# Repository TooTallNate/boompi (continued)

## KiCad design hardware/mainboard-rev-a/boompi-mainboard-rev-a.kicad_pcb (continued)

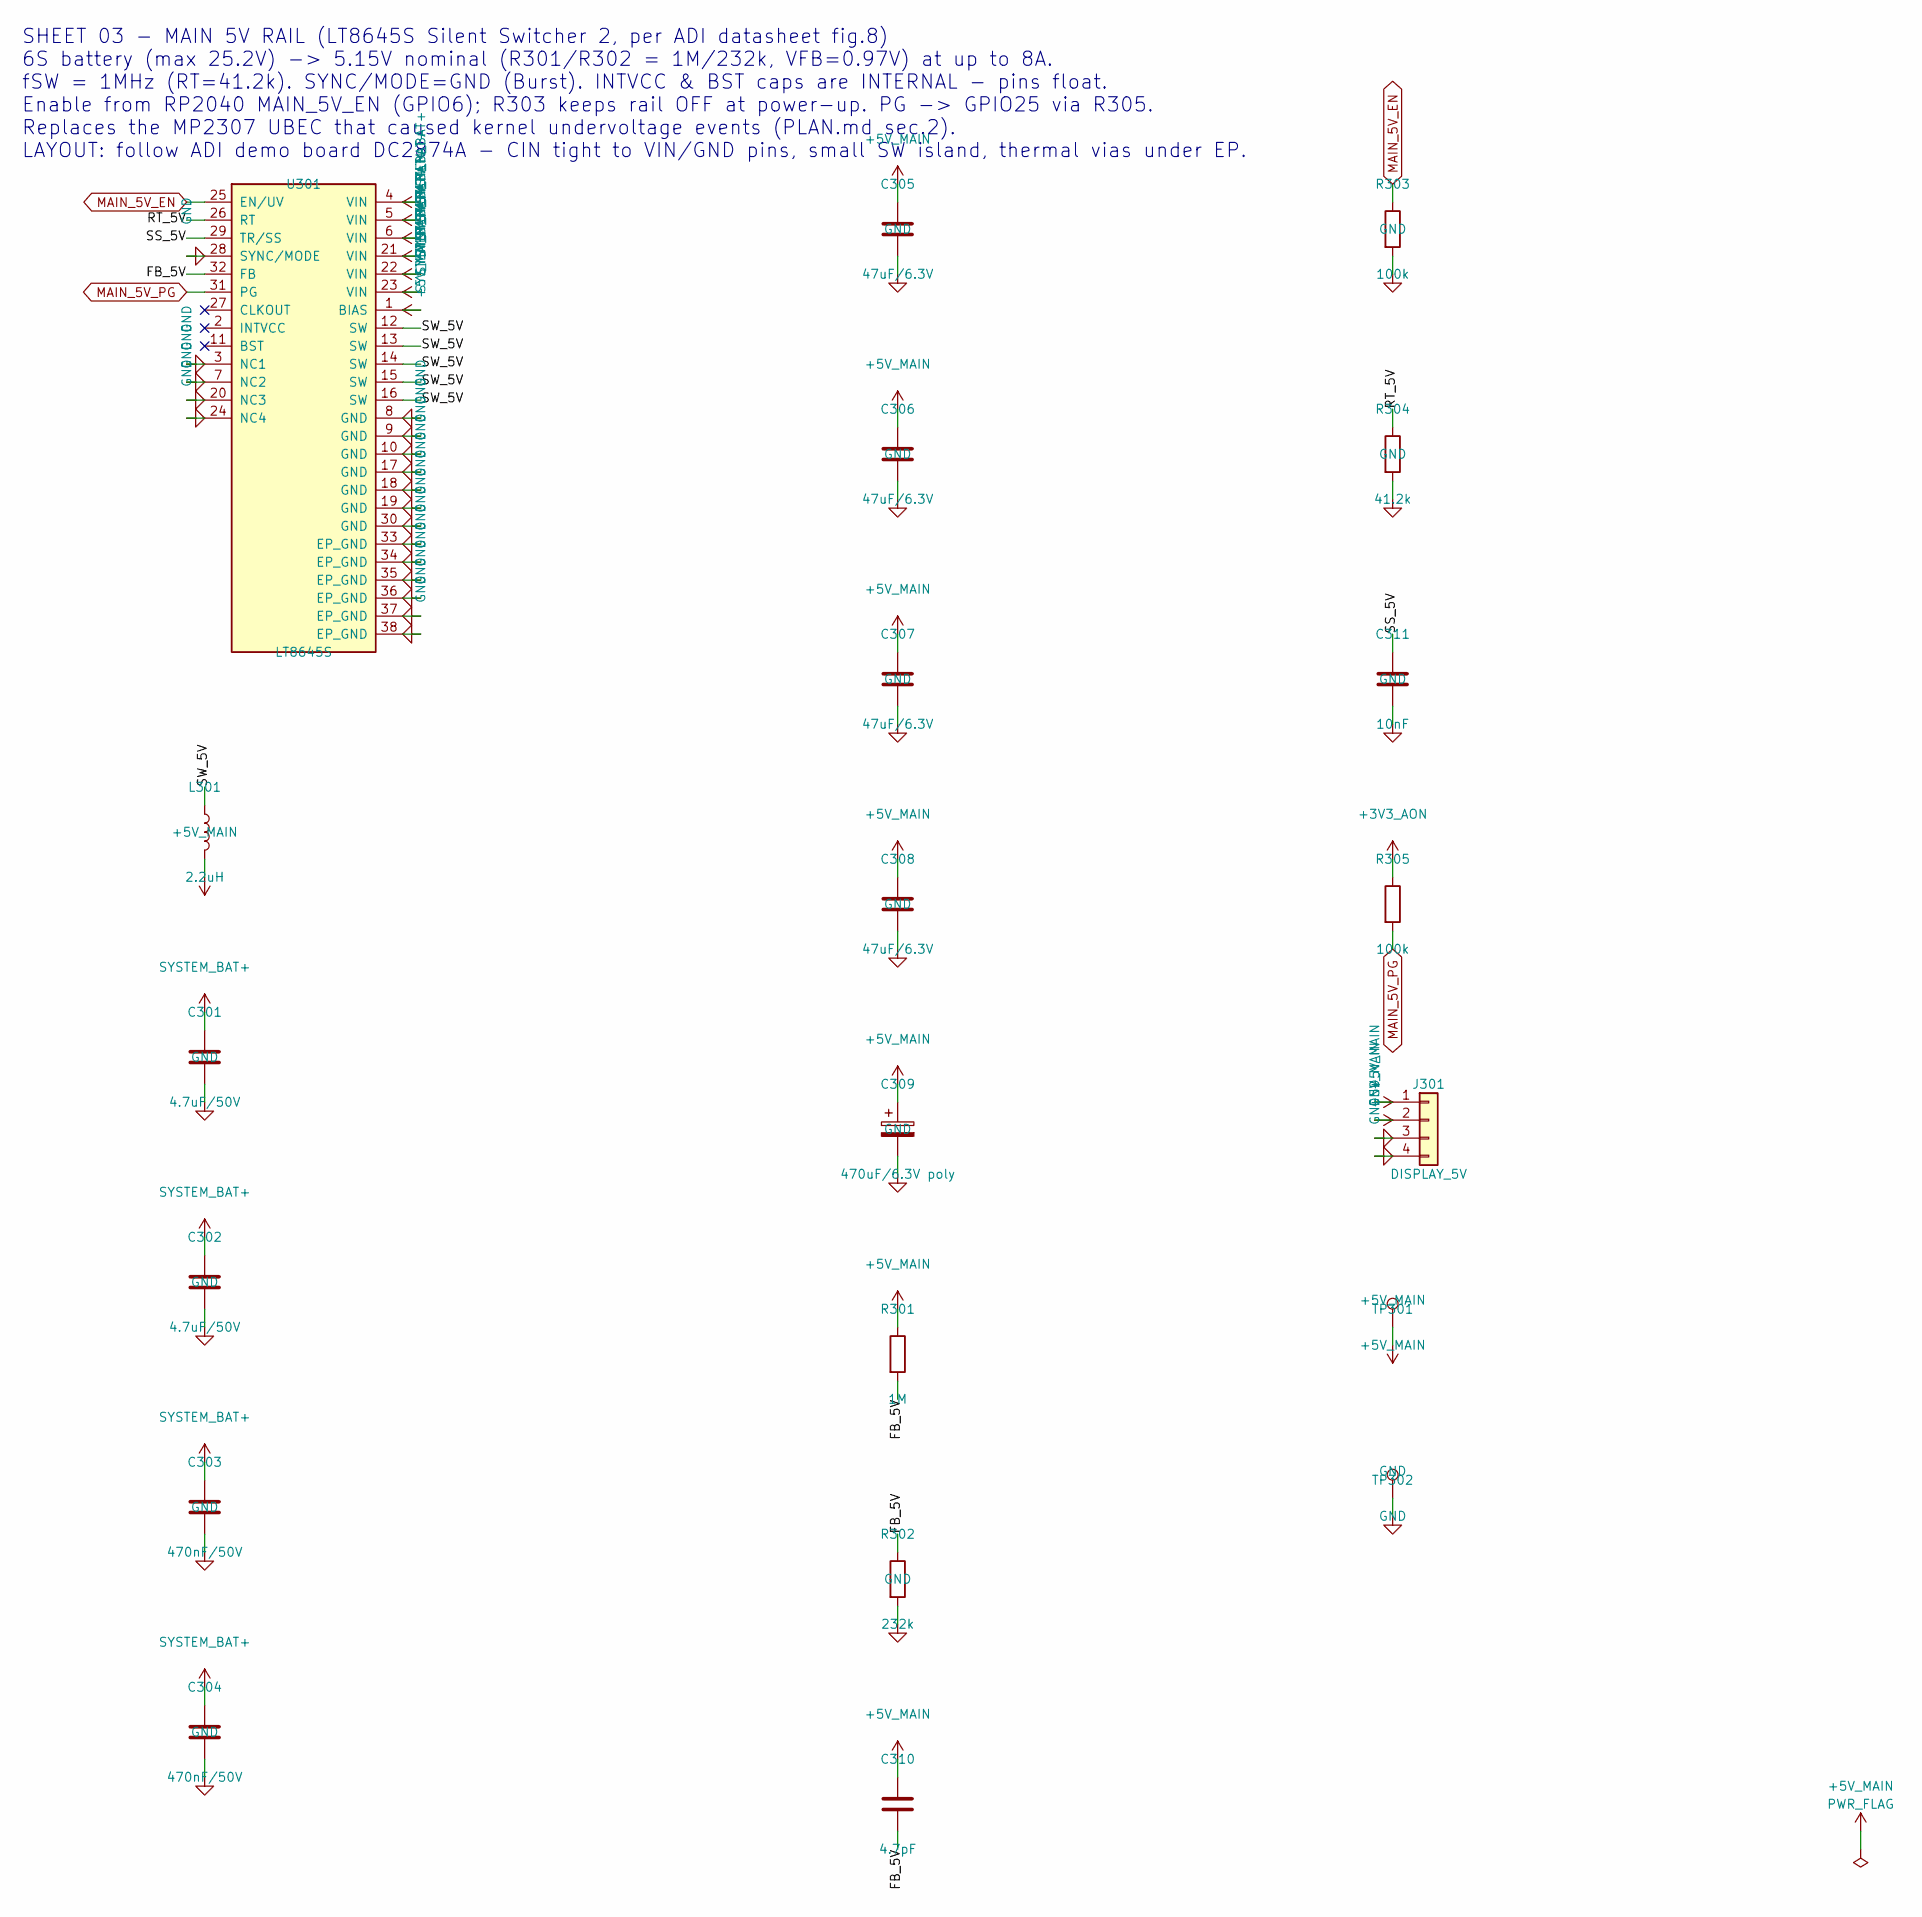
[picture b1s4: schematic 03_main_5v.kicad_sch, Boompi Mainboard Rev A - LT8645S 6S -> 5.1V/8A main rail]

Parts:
C301, C302: 4.7uF/50V; C_1210_3225Metric
C303, C304: 470nF/50V; C_0603_1608Metric
C305, C306, C307, C308: 47uF/6.3V; C_1210_3225Metric
C309: 470uF/6.3V poly; CP_Elec_8x10.5; MPN Panasonic 6TPE470MI
C310: 4.7pF; C_0603_1608Metric
C311: 10nF; C_0603_1608Metric
J301: DISPLAY_5V; JST_XH_B4B-XH-A_1x04_P2.50mm_Vertical; MPN JST B4B-XH-A
L301: 2.2uH; L_Coilcraft_XAL6060-XXX; MPN Coilcraft XEL6060-222MEB
R301: 1M; R_0603_1608Metric
R302: 232k; R_0603_1608Metric
R303, R305: 100k; R_0603_1608Metric
R304: 41.2k; R_0603_1608Metric
TP301: +5V_MAIN; TestPoint_Pad_D1.5mm
TP302: GND; TestPoint_Pad_D1.5mm
U301: LT8645S; LT8645S_LQFN32_4x6mm; MPN ADI LT8645SEV#PBF

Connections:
+3V3_AON: R305.1; also elsewhere on the board
+5V_MAIN: C305.1, C306.1, C307.1, C308.1, C309.1, C310.1, J301.1, J301.2, L301.2, R301.1, TP301.1, U301.1 (BIAS); also elsewhere on the board
/03_MAIN_5V/FB_5V: C310.2, R301.2, R302.1, U301.32 (FB)
/03_MAIN_5V/RT_5V: R304.1, U301.26 (RT)
/03_MAIN_5V/SS_5V: C311.1, U301.29 (TR/SS)
/03_MAIN_5V/SW_5V: L301.1, U301.12 (SW), U301.13 (SW), U301.14 (SW), U301.15 (SW), U301.16 (SW)
GND: C301.2, C302.2, C303.2, C304.2, C305.2, C306.2, C307.2, C308.2, C309.2, C311.2, J301.3, J301.4, R302.2, R303.2, R304.2, TP302.1, U301.3 (NC1), U301.7 (NC2), U301.8 (GND), U301.9 (GND), U301.10 (GND), U301.17 (GND), U301.18 (GND), U301.19 (GND), U301.20 (NC3), U301.24 (NC4), U301.28 (SYNC/MODE), U301.30 (GND), U301.33 (EP_GND), U301.34 (EP_GND), U301.35 (EP_GND), U301.36 (EP_GND), U301.37 (EP_GND), U301.38 (EP_GND); also elsewhere on the board
MAIN_5V_EN: R303.1, U301.25 (EN/UV); also elsewhere on the board
MAIN_5V_PG: R305.2, U301.31 (PG); also elsewhere on the board
SYSTEM_BAT+: C301.1, C302.1, C303.1, C304.1, U301.4 (VIN), U301.5 (VIN), U301.6 (VIN), U301.21 (VIN), U301.22 (VIN), U301.23 (VIN); also elsewhere on the board

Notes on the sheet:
SHEET 03 - MAIN 5V RAIL (LT8645S Silent Switcher 2, per ADI datasheet fig.8) 6S battery (max 25.2V) -> 5.15V nominal (R301/R302 = 1M/232k, VFB=0.97V) at up to 8A. fSW = 1MHz (RT=41.2k). SYNC/MODE=GND (Burst). INTVCC & BST caps are INTERNAL - pins float. Enable from RP2040 MAIN_5V_EN (GPIO6); R303 k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

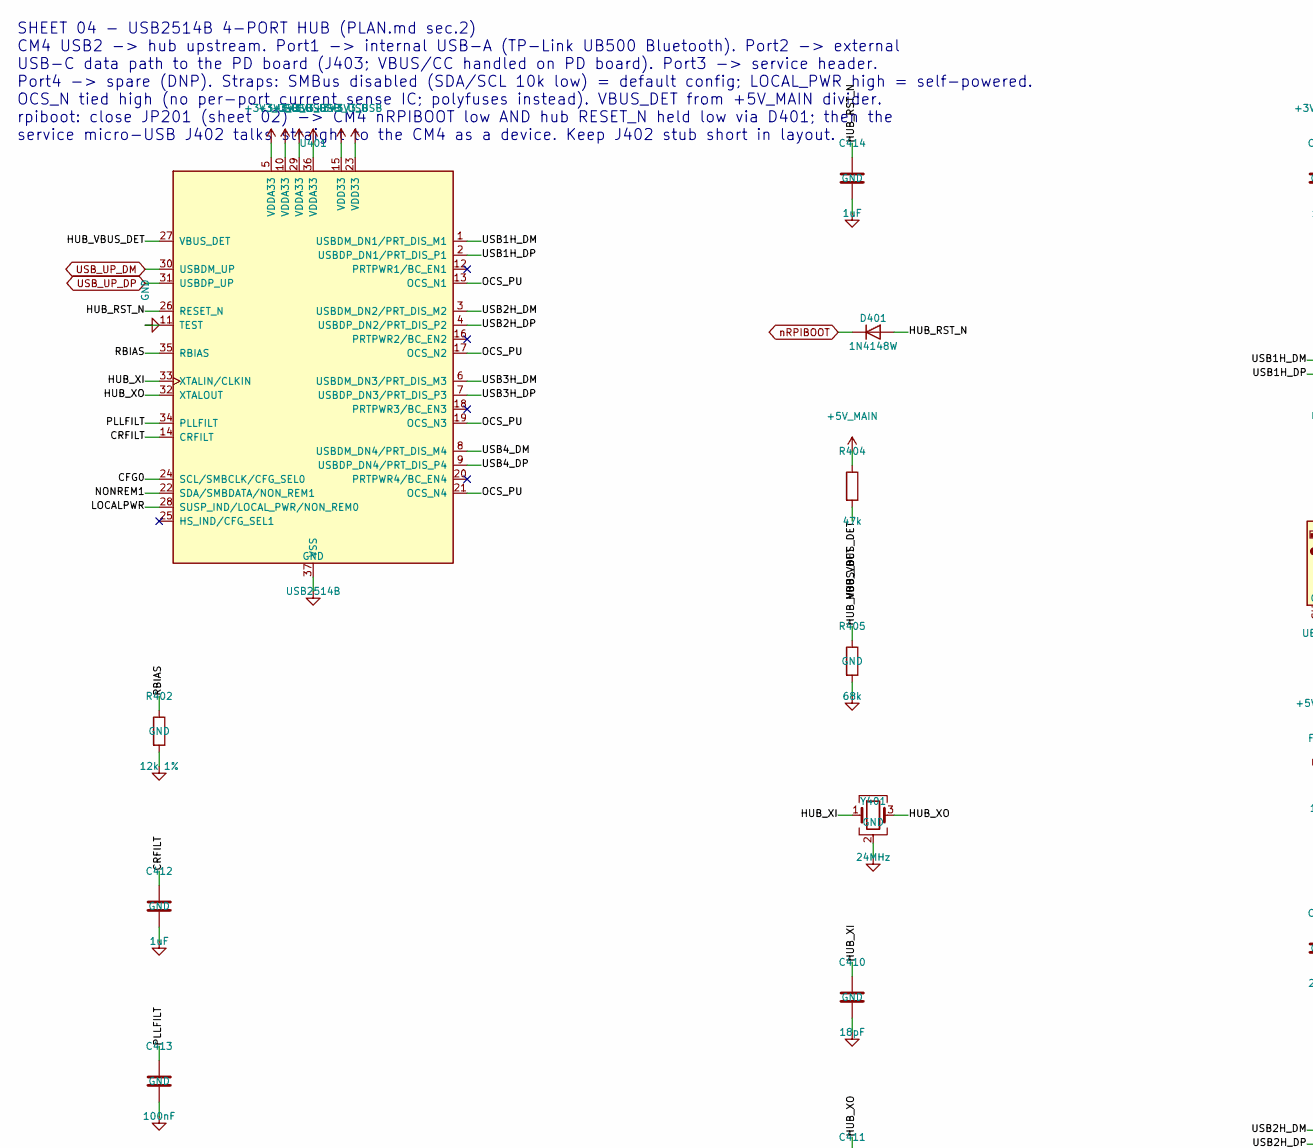
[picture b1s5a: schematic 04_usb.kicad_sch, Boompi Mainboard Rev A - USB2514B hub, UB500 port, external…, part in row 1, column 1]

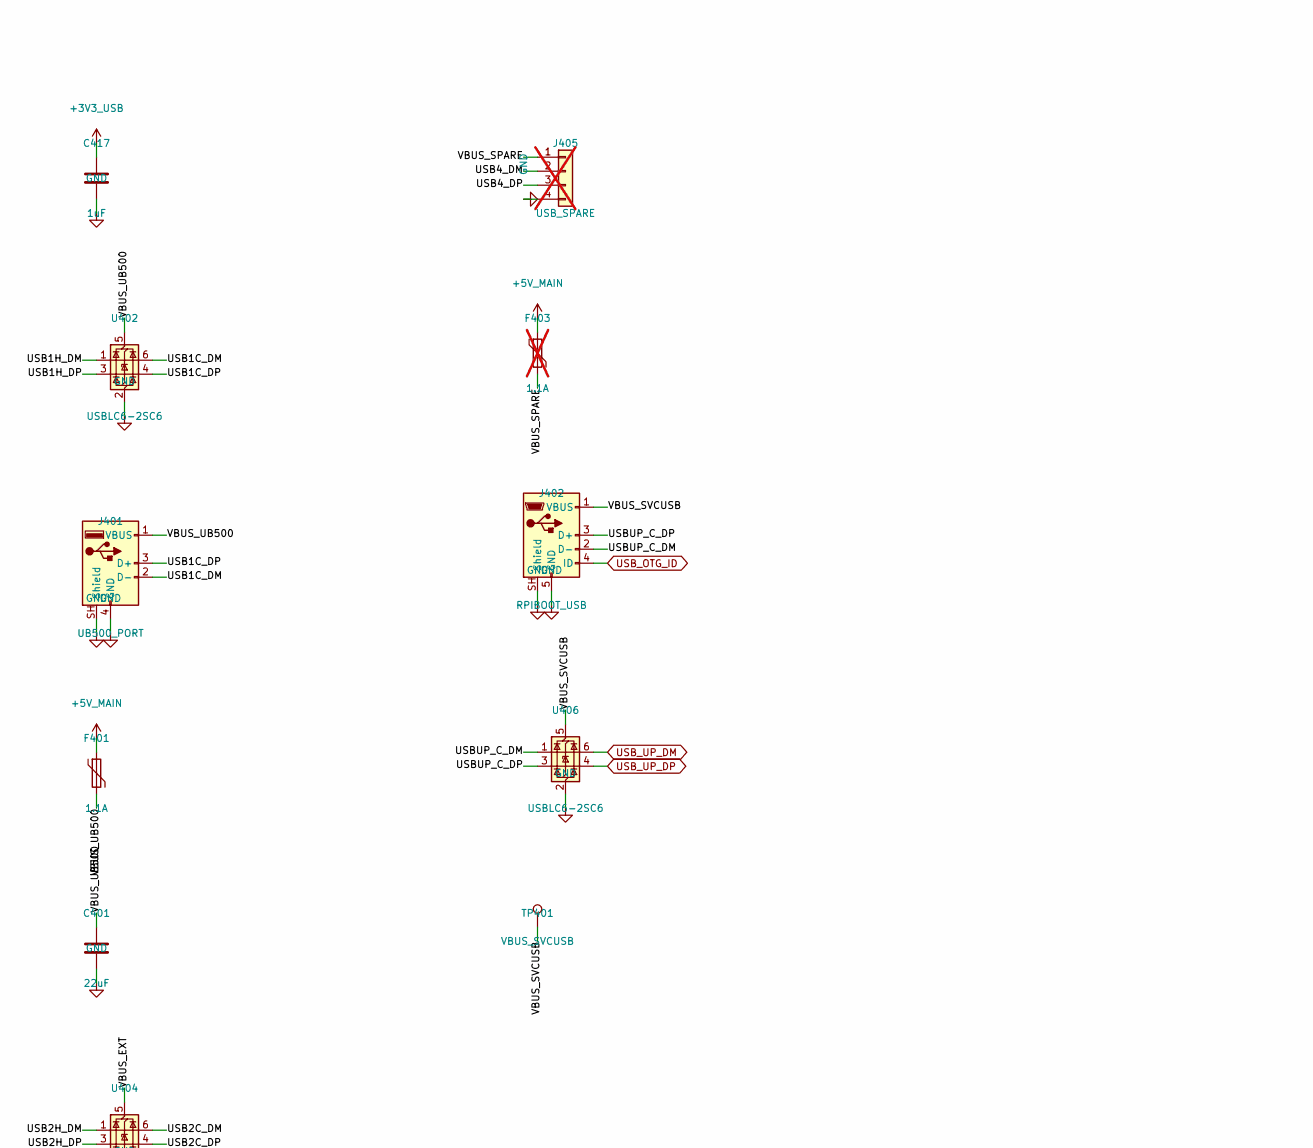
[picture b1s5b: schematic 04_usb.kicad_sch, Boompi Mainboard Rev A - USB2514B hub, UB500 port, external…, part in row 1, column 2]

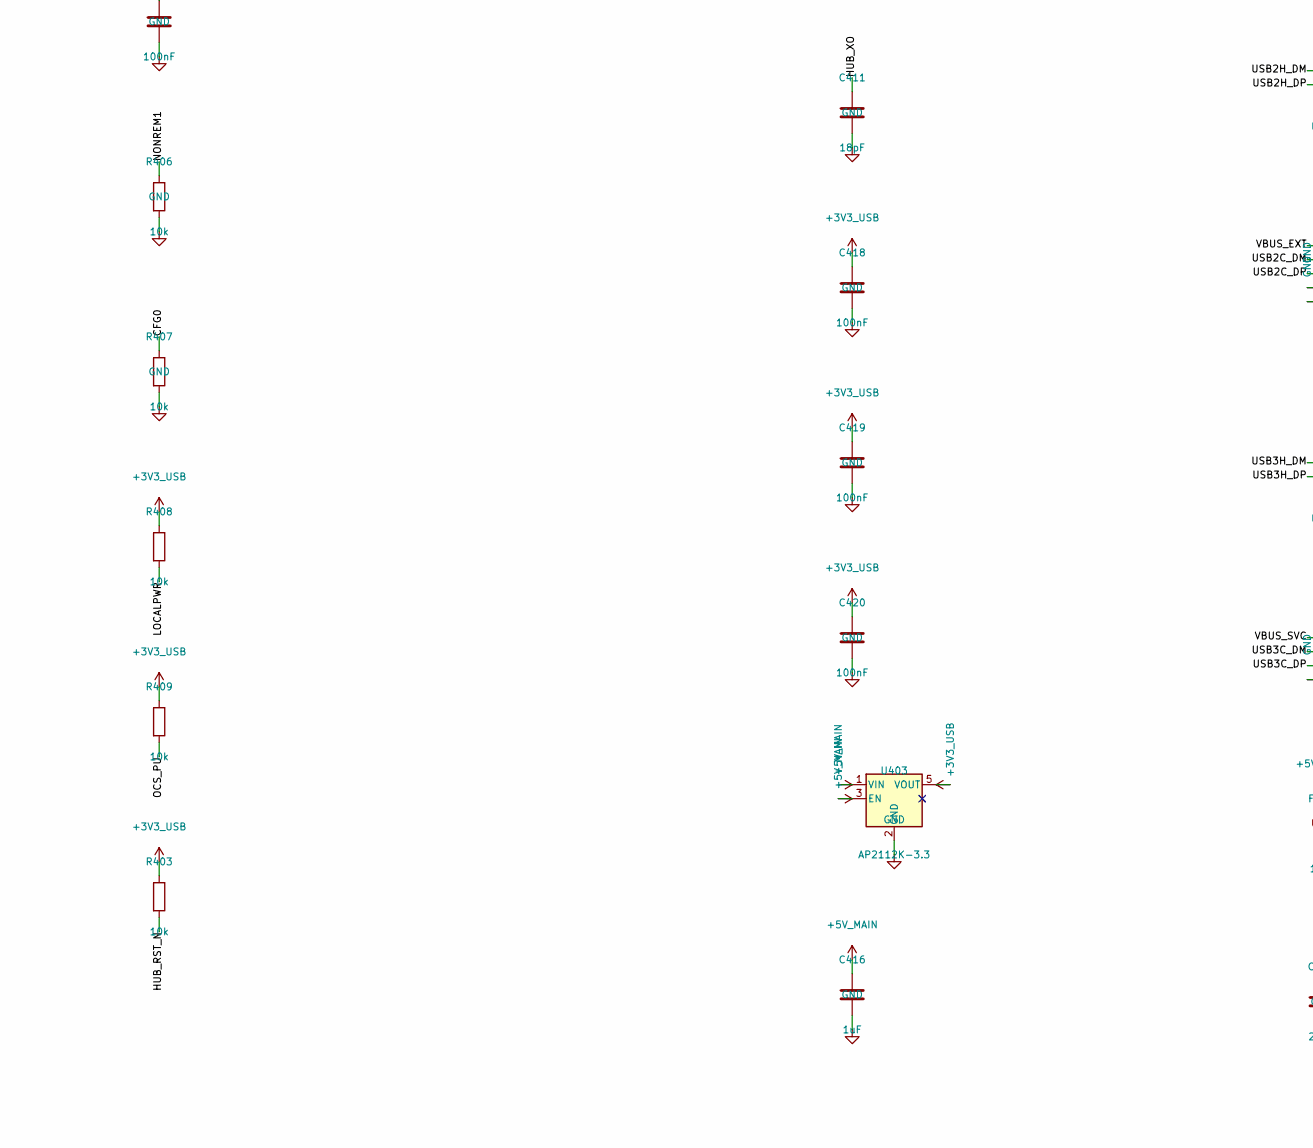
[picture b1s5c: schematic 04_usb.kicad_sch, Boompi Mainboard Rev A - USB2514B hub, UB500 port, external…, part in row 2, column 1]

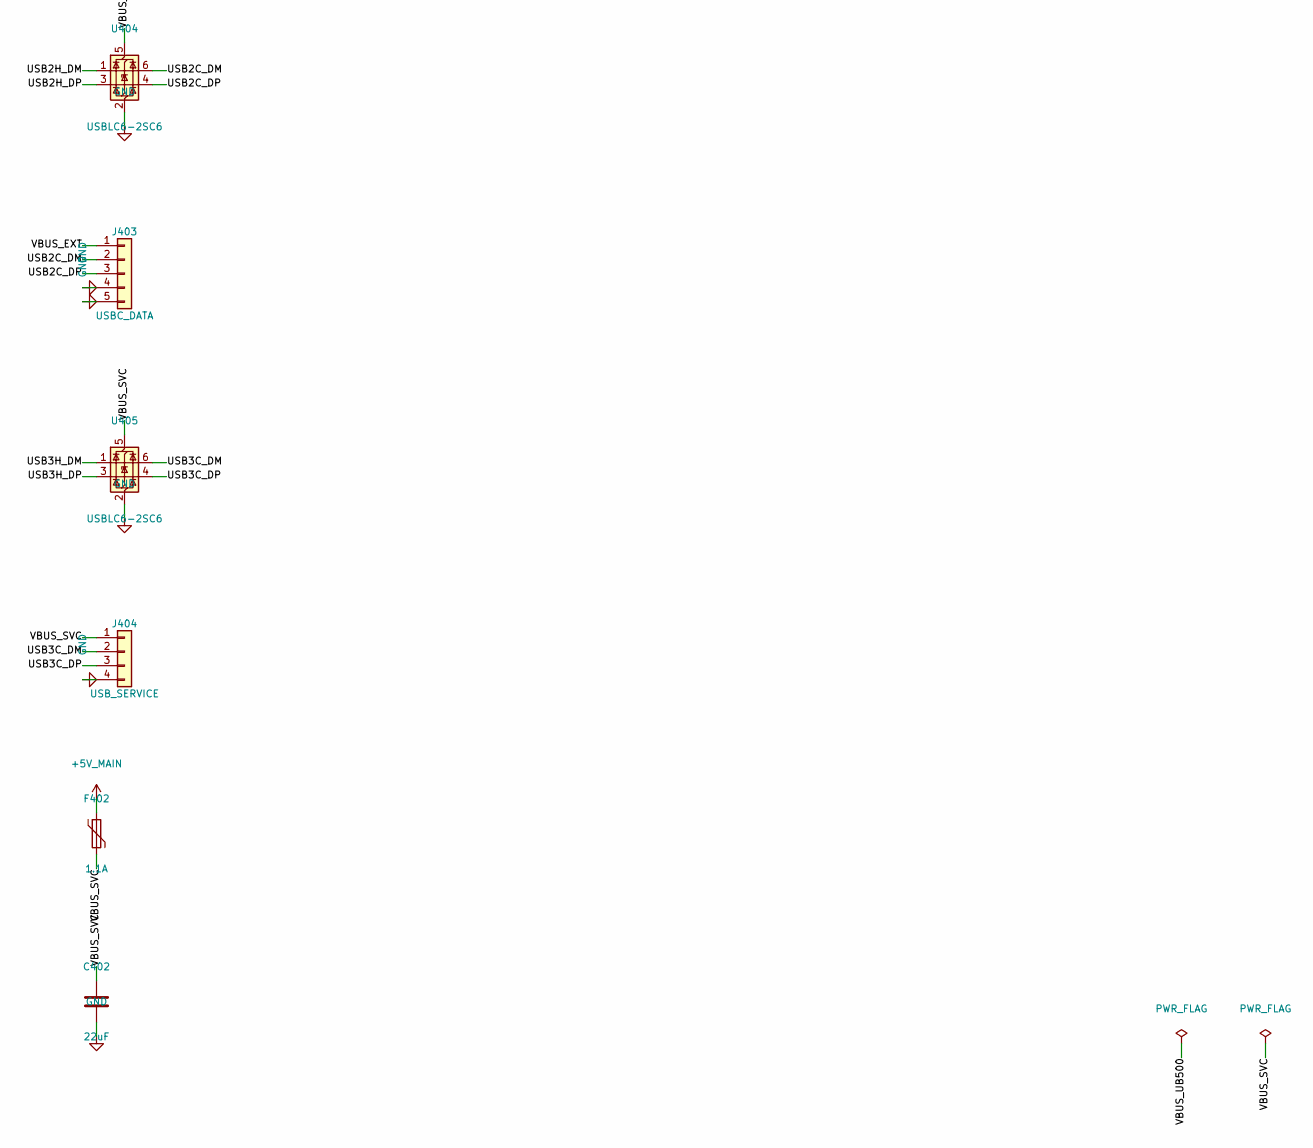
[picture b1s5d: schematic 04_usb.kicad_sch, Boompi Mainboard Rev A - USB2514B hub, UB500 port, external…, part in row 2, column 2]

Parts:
C401, C402: 22uF; C_0805_2012Metric
C410, C411: 18pF; C_0603_1608Metric
C412, C414, C416, C417: 1uF; C_0603_1608Metric
C413, C418, C419, C420: 100nF; C_0603_1608Metric
D401: 1N4148W; D_SOD-123
F401, F402: 1.1A; Fuse_1812_4532Metric; MPN Littelfuse 1812L110
F403: 1.1A; Fuse_1812_4532Metric; not fitted
J401: UB500_PORT; USB_A_Kycon_KUSBX-AS1N-B_Horizontal; MPN Kycon KUSBX-AS1N-B
J402: RPIBOOT_USB; USB_Micro-B_Molex-105017-0001; MPN Molex 105017-0001
J403: USBC_DATA; JST_PH_B5B-PH-K_1x05_P2.00mm_Vertical; MPN JST B5B-PH-K-S
J404: USB_SERVICE; PinHeader_1x04_P2.54mm_Vertical
J405: USB_SPARE; PinHeader_1x04_P2.54mm_Vertical; not fitted
R402: 12k 1%; R_0603_1608Metric
R403, R406, R407, R408, R409: 10k; R_0603_1608Metric
R404: 47k; R_0603_1608Metric
R405: 68k; R_0603_1608Metric
TP401: VBUS_SVCUSB; TestPoint_Pad_D1.5mm
U401: USB2514B; QFN-36-1EP_6x6mm_P0.5mm_EP4.1x4.1mm; MPN Microchip USB2514B-AEZC
U402: USBLC6-2SC6; SOT-23-6; MPN ST USBLC6-2SC6
U403: AP2112K-3.3; SOT-23-5; MPN Diodes AP2112K-3.3TRG1
U404, U405, U406: USBLC6-2SC6; SOT-23-6
Y401: 24MHz; Crystal_SMD_3225-4Pin_3.2x2.5mm; MPN Abracon ABM8-24.000MHZ-B2-T

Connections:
+3V3_USB: C417.1, C418.1, C419.1, C420.1, R403.1, R408.1, R409.1, U401.5 (VDDA33), U401.10 (VDDA33), U401.15 (VDD33), U401.23 (VDD33), U401.29 (VDDA33), U401.36 (VDDA33), U403.5 (VOUT)
+5V_MAIN: C416.1, F401.1, F402.1, F403.1, R404.1, U403.1 (VIN), U403.3 (EN); also elsewhere on the board
/04_USB/CFG0: R407.1, U401.24 (SCL/SMBCLK/CFG_SEL0)
/04_USB/CRFILT: C412.1, U401.14 (CRFILT)
/04_USB/HUB_RST_N: C414.1, D401.2 (A), R403.2, U401.26 (RESET_N)
/04_USB/HUB_VBUS_DET: R404.2, R405.1, U401.27 (VBUS_DET)
/04_USB/HUB_XI: C410.1, U401.33 (XTALIN/CLKIN), Y401.1
/04_USB/HUB_XO: C411.1, U401.32 (XTALOUT), Y401.3
/04_USB/LOCALPWR: R408.2, U401.28 (SUSP_IND/LOCAL_PWR/NON_REM0)
/04_USB/NONREM1: R406.1, U401.22 (SDA/SMBDATA/NON_REM1)
/04_USB/OCS_PU: R409.2, U401.13 (OCS_N1), U401.17 (OCS_N2), U401.19 (OCS_N3), U401.21 (OCS_N4)
/04_USB/PLLFILT: C413.1, U401.34 (PLLFILT)
/04_USB/RBIAS: R402.1, U401.35 (RBIAS)
/04_USB/USB1C_DM: J401.2 (D-), U402.6 (I/O1)
/04_USB/USB1C_DP: J401.3 (D+), U402.4 (I/O2)
/04_USB/USB1H_DM: U401.1 (USBDM_DN1/PRT_DIS_M1), U402.1 (I/O1)
/04_USB/USB1H_DP: U401.2 (USBDP_DN1/PRT_DIS_P1), U402.3 (I/O2)
/04_USB/USB2C_DM: J403.2, U404.6 (I/O1)
/04_USB/USB2C_DP: J403.3, U404.4 (I/O2)
/04_USB/USB2H_DM: U401.3 (USBDM_DN2/PRT_DIS_M2), U404.1 (I/O1)
/04_USB/USB2H_DP: U401.4 (USBDP_DN2/PRT_DIS_P2), U404.3 (I/O2)
/04_USB/USB3C_DM: J404.2, U405.6 (I/O1)
/04_USB/USB3C_DP: J404.3, U405.4 (I/O2)
/04_USB/USB3H_DM: U401.6 (USBDM_DN3/PRT_DIS_M3), U405.1 (I/O1)
/04_USB/USB3H_DP: U401.7 (USBDP_DN3/PRT_DIS_P3), U405.3 (I/O2)
/04_USB/USB4_DM: J405.2, U401.8 (USBDM_DN4/PRT_DIS_M4)
/04_USB/USB4_DP: J405.3, U401.9 (USBDP_DN4/PRT_DIS_P4)
/04_USB/USBUP_C_DM: J402.2 (D-), U406.1 (I/O1)
/04_USB/USBUP_C_DP: J402.3 (D+), U406.3 (I/O2)
/04_USB/VBUS_EXT: J403.1, U404.5 (VBUS)
/04_USB/VBUS_SPARE: F403.2, J405.1
/04_USB/VBUS_SVC: C402.1, F402.2, J404.1, U405.5 (VBUS)
/04_USB/VBUS_SVCUSB: J402.1 (VBUS), TP401.1, U406.5 (VBUS)
/04_USB/VBUS_UB500: C401.1, F401.2, J401.1 (VBUS), U402.5 (VBUS)
GND: C401.2, C402.2, C410.2, C411.2, C412.2, C413.2, C414.2, C416.2, C417.2, C418.2, C419.2, C420.2, J401.4 (GND), J401.SH (Shield), J402.5 (GND), J402.SH (Shield), J403.4, J403.5, J404.4, J405.4, R402.2, R405.2, R406.2, R407.2, U401.11 (TEST), U401.37 (VSS), U402.2 (GND), U403.2 (GND), U404.2 (GND), U405.2 (GND), U406.2 (GND), Y401.2 (G), Y401.4 (G); also elsewhere on the board
USB_OTG_ID: J402.4 (ID); also elsewhere on the board
USB_UP_DM: U401.30 (USBDM_UP), U406.6 (I/O1); also elsewhere on the board
USB_UP_DP: U401.31 (USBDP_UP), U406.4 (I/O2); also elsewhere on the board
nRPIBOOT: D401.1 (K); also elsewhere on the board

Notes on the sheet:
SHEET 04 - USB2514B 4-PORT HUB (PLAN.md sec.2) CM4 USB2 -> hub upstream. Port1 -> internal USB-A (TP-Link UB500 Bluetooth). Port2 -> external USB-C data path to the PD board (J403; VBUS/CC handled on PD board). Port3 -> service header. Port4 -> spare (DNP). Straps: SMBus disabled (SDA/SCL 10k low) 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

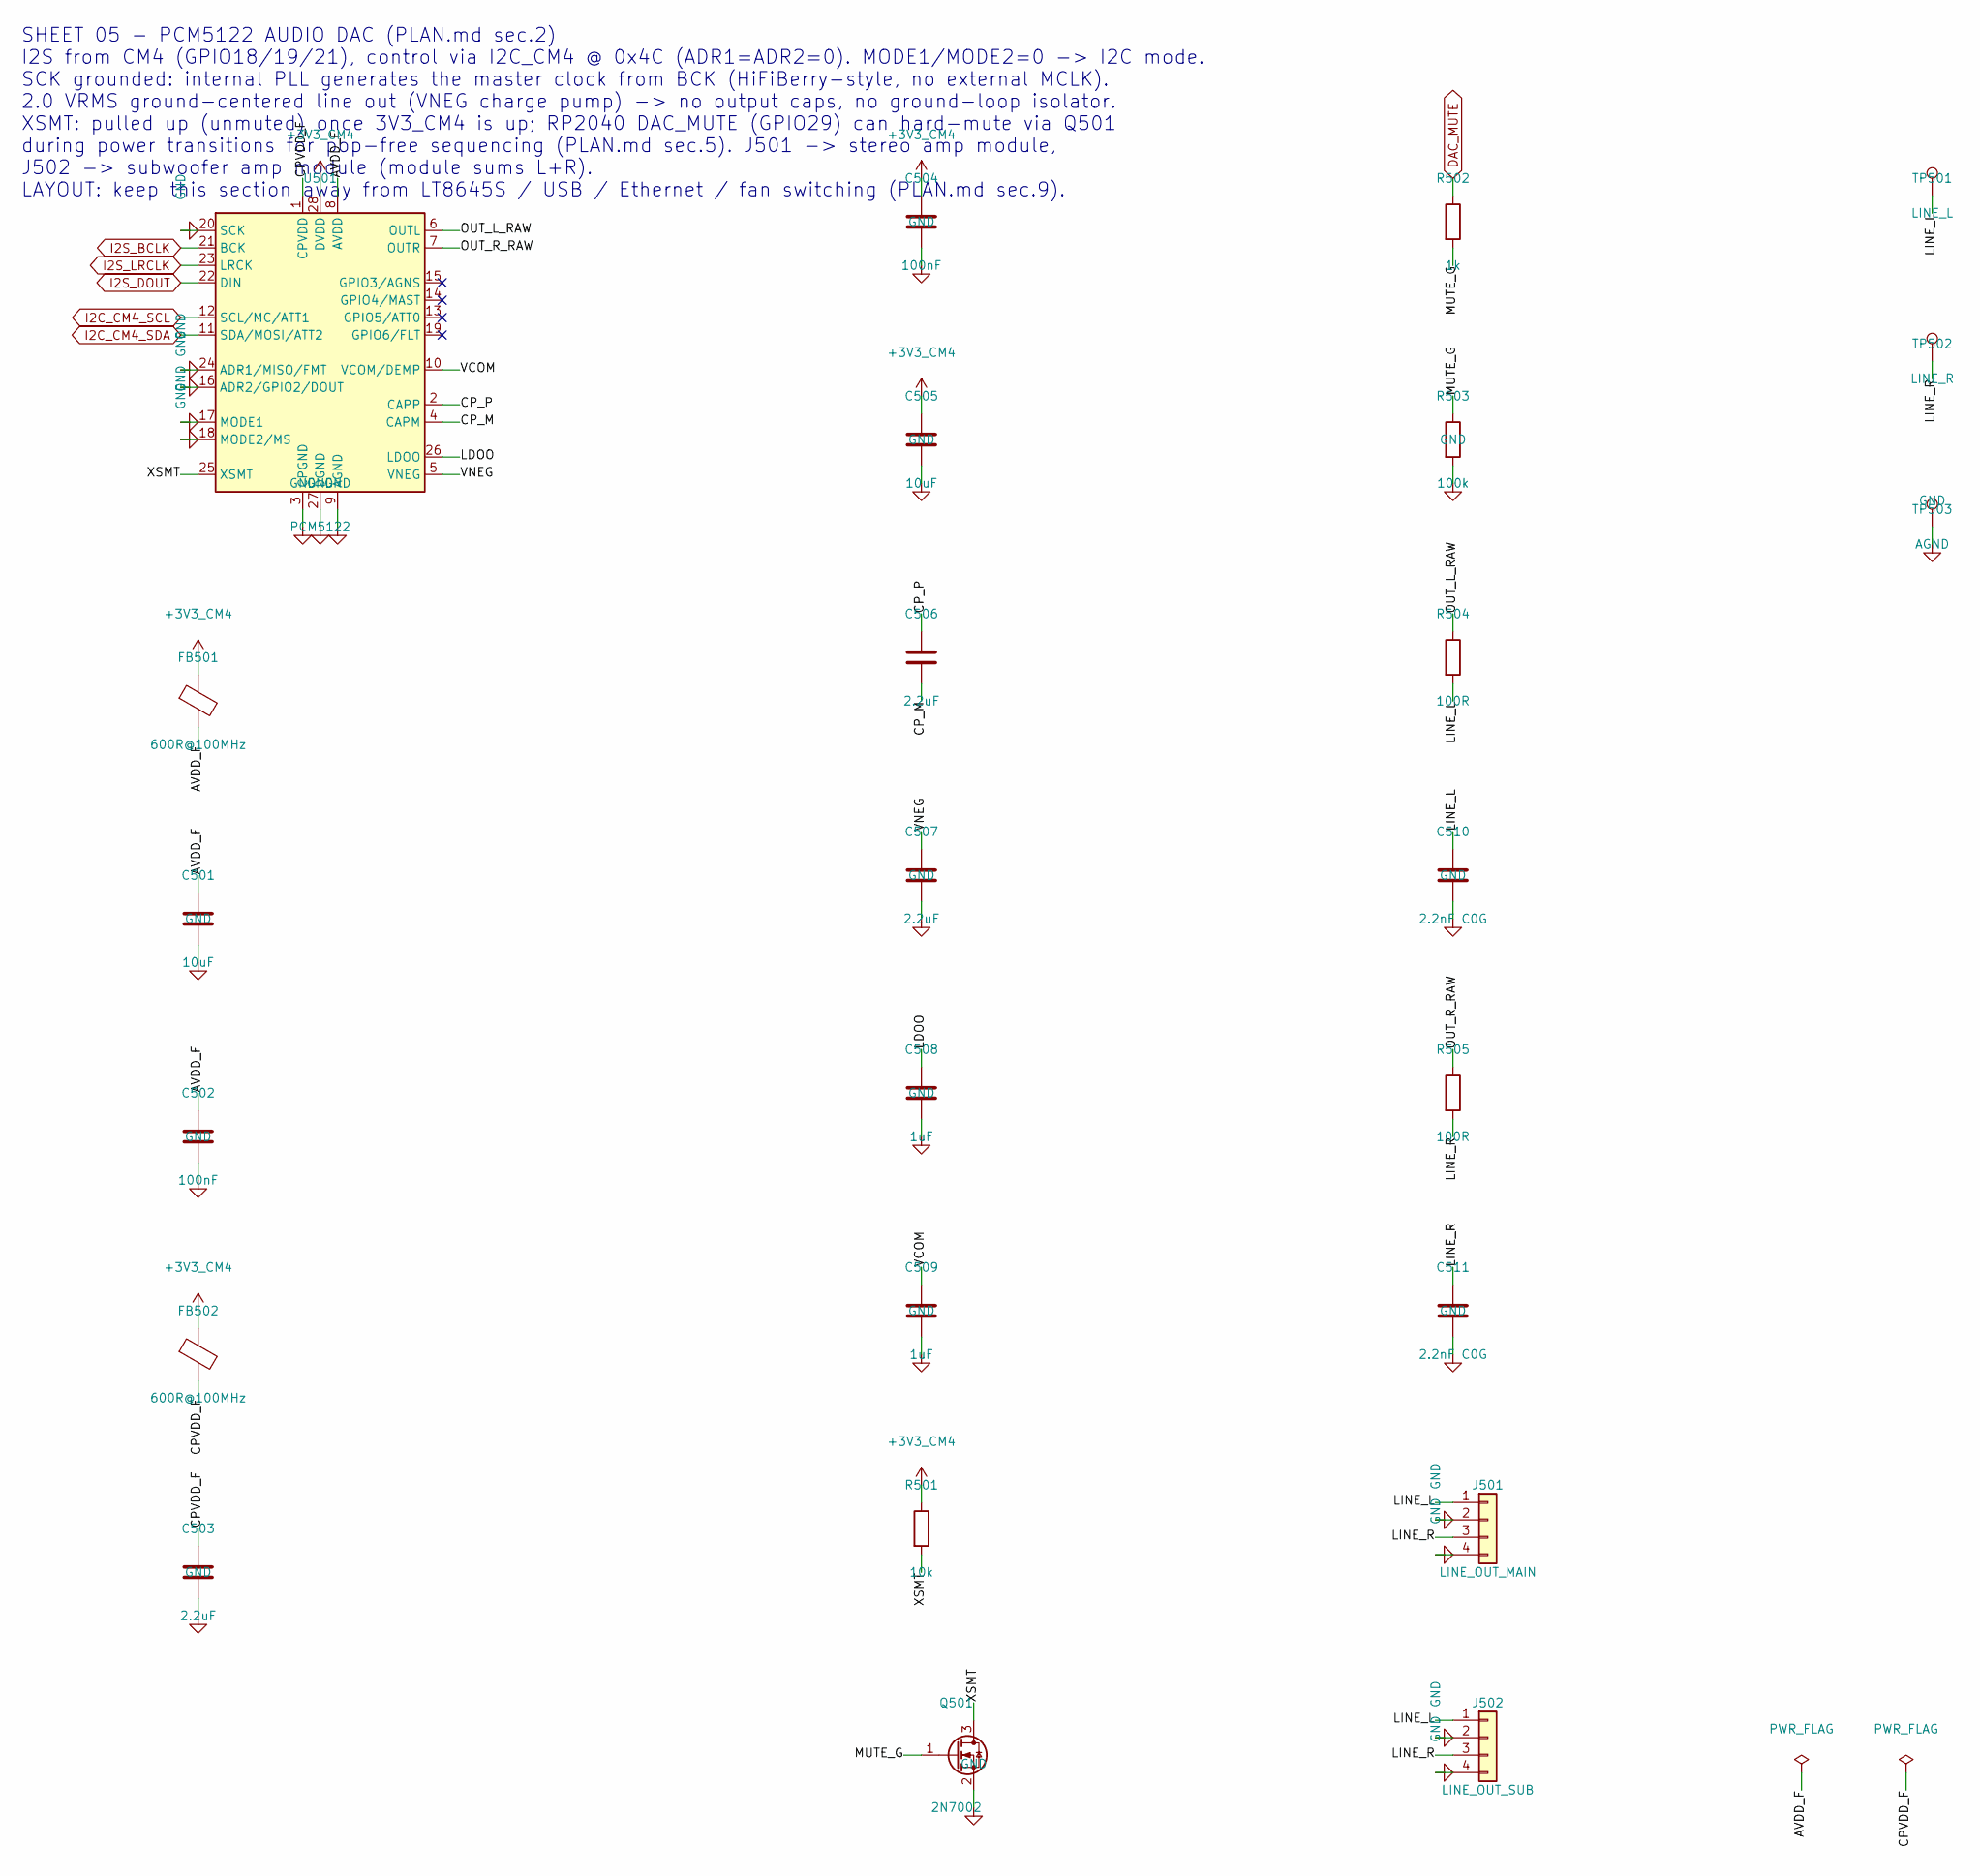
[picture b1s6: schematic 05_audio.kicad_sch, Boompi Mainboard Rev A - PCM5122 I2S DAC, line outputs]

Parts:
C501, C505: 10uF; C_0805_2012Metric
C502, C504: 100nF; C_0603_1608Metric
C503, C506, C507: 2.2uF; C_0603_1608Metric
C508, C509: 1uF; C_0603_1608Metric
C510, C511: 2.2nF C0G; C_0603_1608Metric
FB501, FB502: 600R@100MHz; L_0805_2012Metric; MPN Murata BLM21PG600SN1D
J501: LINE_OUT_MAIN; JST_PH_B4B-PH-K_1x04_P2.00mm_Vertical; MPN JST B4B-PH-K-S
J502: LINE_OUT_SUB; JST_PH_B4B-PH-K_1x04_P2.00mm_Vertical; MPN JST B4B-PH-K-S
Q501: 2N7002; SOT-23
R501: 10k; R_0603_1608Metric
R502: 1k; R_0603_1608Metric
R503: 100k; R_0603_1608Metric
R504, R505: 100R; R_0603_1608Metric
TP501: LINE_L; TestPoint_Pad_D1.5mm
TP502: LINE_R; TestPoint_Pad_D1.5mm
TP503: AGND; TestPoint_Pad_D1.5mm
U501: PCM5122; TSSOP-28_4.4x9.7mm_P0.65mm; MPN TI PCM5122PW

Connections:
+3V3_CM4: C504.1, C505.1, FB501.1, FB502.1, R501.1, U501.28 (DVDD); also elsewhere on the board
/05_AUDIO/AVDD_F: C501.1, C502.1, FB501.2, U501.8 (AVDD)
/05_AUDIO/CPVDD_F: C503.1, FB502.2, U501.1 (CPVDD)
/05_AUDIO/CP_M: C506.2, U501.4 (CAPM)
/05_AUDIO/CP_P: C506.1, U501.2 (CAPP)
/05_AUDIO/LDOO: C508.1, U501.26 (LDOO)
/05_AUDIO/LINE_L: C510.1, J501.1, J502.1, R504.2, TP501.1
/05_AUDIO/LINE_R: C511.1, J501.3, J502.3, R505.2, TP502.1
/05_AUDIO/MUTE_G: Q501.1 (G), R502.2, R503.1
/05_AUDIO/OUT_L_RAW: R504.1, U501.6 (OUTL)
/05_AUDIO/OUT_R_RAW: R505.1, U501.7 (OUTR)
/05_AUDIO/VCOM: C509.1, U501.10 (VCOM/DEMP)
/05_AUDIO/VNEG: C507.1, U501.5 (VNEG)
/05_AUDIO/XSMT: Q501.3 (D), R501.2, U501.25 (XSMT)
DAC_MUTE: R502.1; also elsewhere on the board
GND: C501.2, C502.2, C503.2, C504.2, C505.2, C507.2, C508.2, C509.2, C510.2, C511.2, J501.2, J501.4, J502.2, J502.4, Q501.2 (S), R503.2, TP503.1, U501.3 (CPGND), U501.9 (AGND), U501.16 (ADR2/GPIO2/DOUT), U501.17 (MODE1), U501.18 (MODE2/MS), U501.20 (SCK), U501.24 (ADR1/MISO/FMT), U501.27 (DGND); also elsewhere on the board
I2C_CM4_SCL: U501.12 (SCL/MC/ATT1); also elsewhere on the board
I2C_CM4_SDA: U501.11 (SDA/MOSI/ATT2); also elsewhere on the board
I2S_BCLK: U501.21 (BCK); also elsewhere on the board
I2S_DOUT: U501.22 (DIN); also elsewhere on the board
I2S_LRCLK: U501.23 (LRCK); also elsewhere on the board

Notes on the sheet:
SHEET 05 - PCM5122 AUDIO DAC (PLAN.md sec.2) I2S from CM4 (GPIO18/19/21), control via I2C_CM4 @ 0x4C (ADR1=ADR2=0). MODE1/MODE2=0 -> I2C mode. SCK grounded: internal PLL generates the master clock from BCK (HiFiBerry-style, no external MCLK). 2.0 VRMS ground-centered line out (VNEG charge pump) -> 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

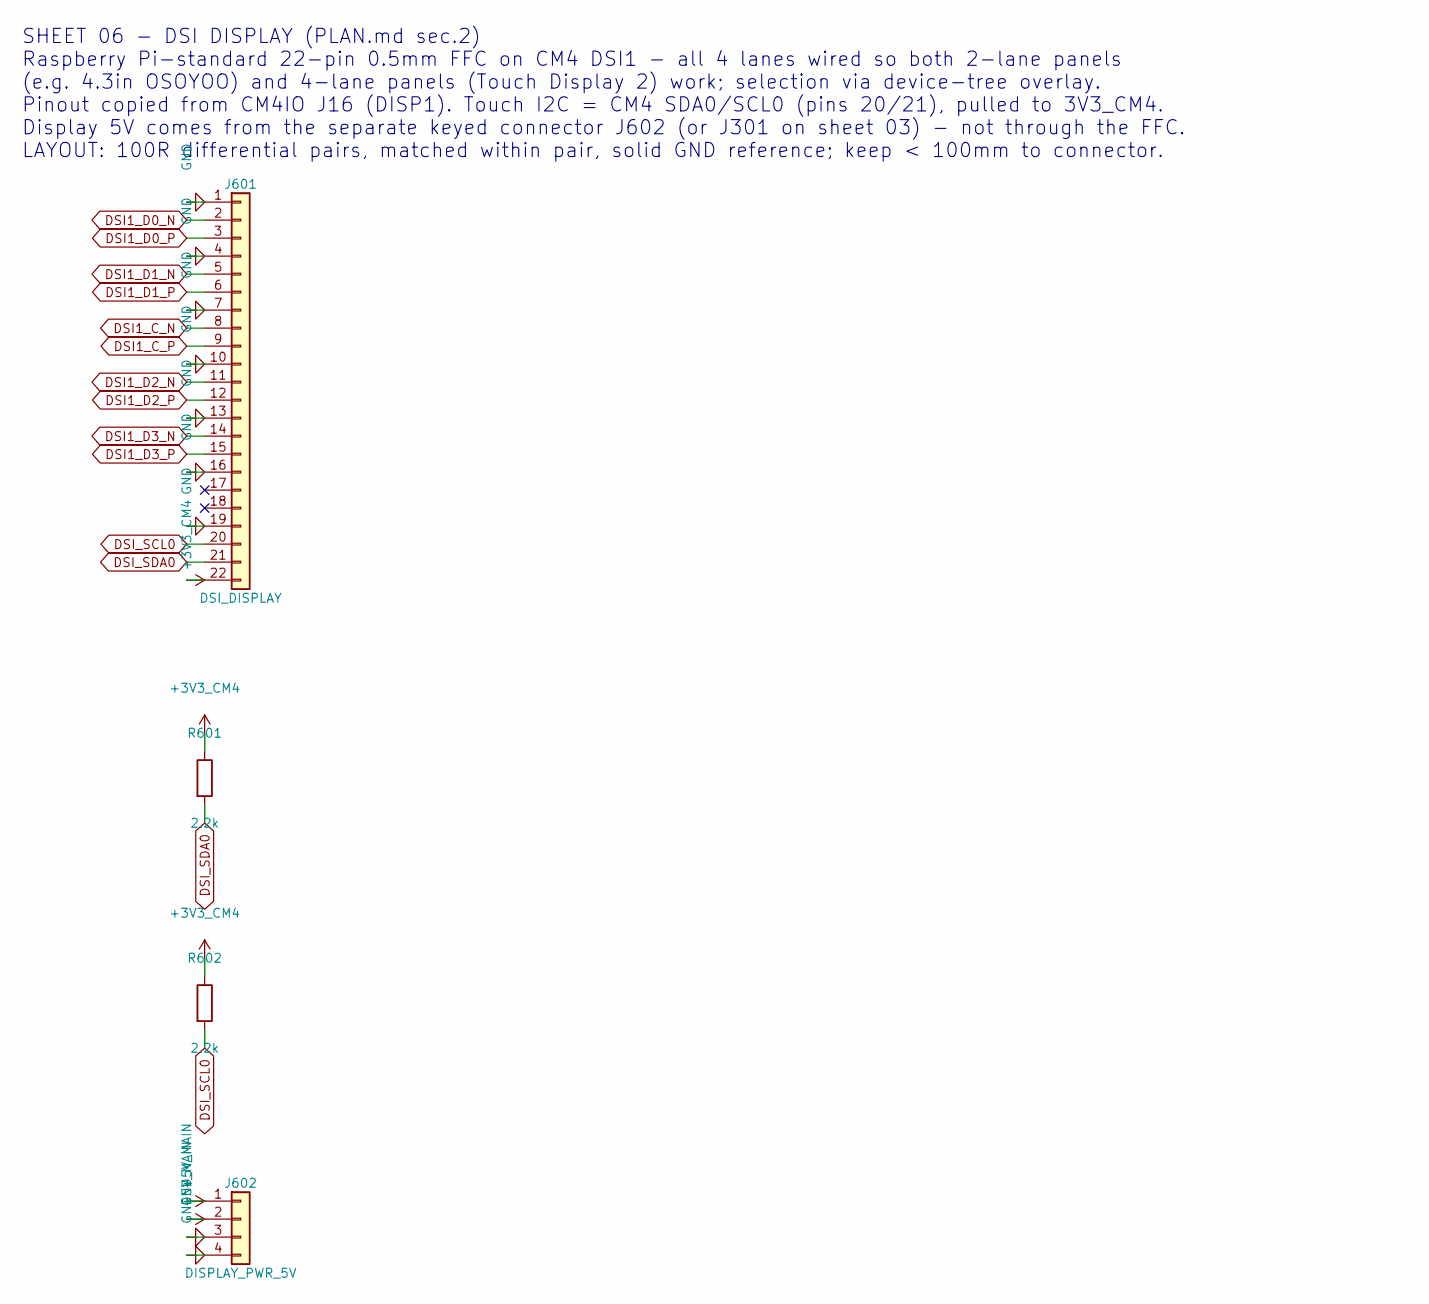
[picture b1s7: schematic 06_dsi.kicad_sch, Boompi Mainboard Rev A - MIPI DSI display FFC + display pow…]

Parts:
J601: DSI_DISPLAY; Hirose_FH12-22S-0.5SH_1x22-1MP_P0.50mm_Horizontal; MPN Hirose FH12-22S-0.5SH(55)
J602: DISPLAY_PWR_5V; JST_XH_B4B-XH-A_1x04_P2.50mm_Vertical; MPN JST B4B-XH-A
R601, R602: 2.2k; R_0603_1608Metric

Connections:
+3V3_CM4: J601.22, R601.1, R602.1; also elsewhere on the board
+5V_MAIN: J602.1, J602.2; also elsewhere on the board
DSI1_C_N: J601.8; also elsewhere on the board
DSI1_C_P: J601.9; also elsewhere on the board
DSI1_D0_N: J601.2; also elsewhere on the board
DSI1_D0_P: J601.3; also elsewhere on the board
DSI1_D1_N: J601.5; also elsewhere on the board
DSI1_D1_P: J601.6; also elsewhere on the board
DSI1_D2_N: J601.11; also elsewhere on the board
DSI1_D2_P: J601.12; also elsewhere on the board
DSI1_D3_N: J601.14; also elsewhere on the board
DSI1_D3_P: J601.15; also elsewhere on the board
DSI_SCL0: J601.20, R602.2; also elsewhere on the board
DSI_SDA0: J601.21, R601.2; also elsewhere on the board
GND: J601.1, J601.4, J601.7, J601.10, J601.13, J601.16, J601.19, J602.3, J602.4; also elsewhere on the board

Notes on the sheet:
SHEET 06 - DSI DISPLAY (PLAN.md sec.2) Raspberry Pi-standard 22-pin 0.5mm FFC on CM4 DSI1 - all 4 lanes wired so both 2-lane panels (e.g. 4.3in OSOYOO) and 4-lane panels (Touch Display 2) work; selection via device-tree overlay. Pinout copied from CM4IO J16 (DISP1). Touch I2C = CM4 SDA0/SCL0 (pins 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
